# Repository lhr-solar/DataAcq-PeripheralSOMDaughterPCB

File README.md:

# Telemetry Peripheral SOM Daughterboard IMU
Author: Frank Li and Jim Fang

This board takes inputs from an IMU, airflow sensor, and three temp sensors and interfaces with the BPS Leader SOM.

## BOM

[**Mouser Cart**](https://www.mouser.com/ProjectManager/ProjectDetail.aspx?AccessID=6005ad65a9)

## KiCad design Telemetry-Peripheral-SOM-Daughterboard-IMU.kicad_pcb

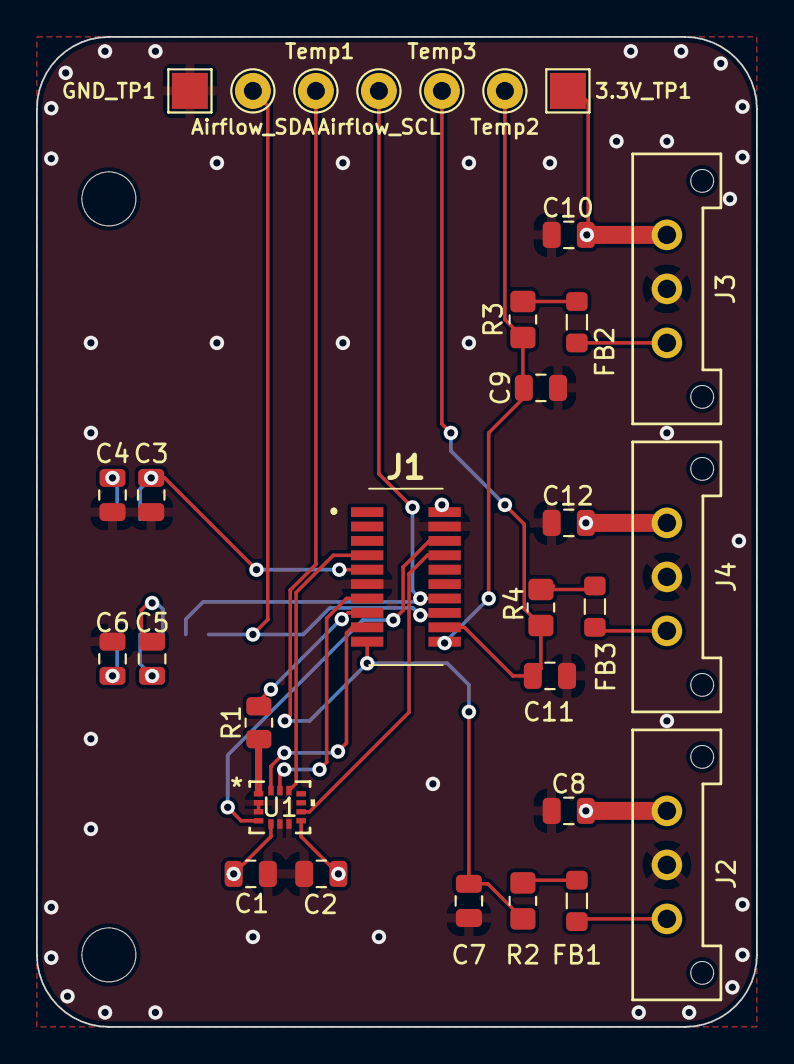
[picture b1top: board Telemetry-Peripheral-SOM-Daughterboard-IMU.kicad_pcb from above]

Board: 2 copper layers, 40.0 x 55.0 mm, 34 parts (1 on the bottom side), 24 nets.

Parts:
3.3V_TP1: TestPoint; TestPoint_Pad_2.0x2.0mm
Airflow_SCL: TestPoint; TestPoint_THTPad_D2.0mm_Drill1.0mm
Airflow_SDA: TestPoint; TestPoint_THTPad_D2.0mm_Drill1.0mm
C1, C2, C3, C4, C5, C8, C10, C12: 0.1u; C_0805_2012Metric
C6: 1u; C_0805_2012Metric
C7, C9, C11: 10n; C_0805_2012Metric
FB1, FB2, FB3: 2.2k; L_0805_2012Metric_Pad1.05x1.20mm_HandSolder
GND_TP1: TestPoint; TestPoint_Pad_2.0x2.0mm
IC1: FS3000-1015; FS30001015
J1: Conn_02x10_Odd_Even; Molex_53307-2071
J2, J3, J4: Conn_01x03_Pin; Molex_MicroFit3.0_1x3xP3.00mm_PolarizingPeg_Vertical
MH1, MH2: M.3; MountingHole_3mm
R1: 50; R_0805_2012Metric
R2, R3, R4: 3k; R_0805_2012Metric_Pad1.20x1.40mm_HandSolder
Temp1, Temp2, Temp3: TestPoint; TestPoint_THTPad_D2.0mm_Drill1.0mm
U1: LSM6DSV; LGA14-L_2P59X3P1X0P5_STM

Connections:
+3.3V: 3.3V_TP1.1, C1.1, C2.1, C3.1, C8.1, C10.1, C12.1, IC1.2 (VIN), J1.2, J1.9, J2.1, J3.1, J4.1, U1.5 (VDD_IO), U1.8 (VDD)
/I2C1_SCL: Airflow_SCL.1, IC1.7 (SCL), J1.14
/I2C1_SDA: Airflow_SDA.1, IC1.6 (SDA), J1.16
/I2C2_SCL: J1.8, U1.9 (INT2)
/I2C2_SDA: J1.6, U1.4 (INT1)
/PA1: C9.1, J1.20, R3.1, Temp2.1
/PA2: C11.1, J1.18, R4.1, Temp3.1
/SPI1_MISO: J1.15, R1.1
/SPI1_MOSI: J1.17, U1.14 (SDA)
/SPI1_NSS: C7.1, J1.19, R2.1, Temp1.1
/SPI1_SCK: J1.13, U1.13 (SCL)
/SPI2_NSS: J1.7, U1.12 (CS)
GND: C1.2, C2.2, C3.2, C4.2, C6.2, C7.2, C8.2, C9.2, C10.2, C11.2, C12.2, GND_TP1.1, IC1.3 (GND), J1.4, J1.11, J2.2, J3.2, J4.2, U1.2 (SDX), U1.3 (SCX), U1.6 (GND), U1.7 (GND)
unnamed: FB1.1, R2.2
unnamed: FB2.1, R3.2
unnamed: FB3.1, R4.2
unnamed: C5.1, IC1.8 (TP1)
unnamed: C5.2, IC1.9 (TP2)
unnamed: C6.1, IC1.10 (VCM)
unnamed: C4.1, IC1.1 (VREG)
unnamed: FB1.2, J2.3
unnamed: FB2.2, J3.3
unnamed: FB3.2, J4.3
unnamed: R1.2, U1.1 (SDO/SA0)

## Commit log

2023-08-28 very basic daughterboard
2023-09-02 Update Telemetry-Peripheral-SOM-Daughterboard-IMU.kicad_sch
    add impedance matching resistor
2023-09-02 Update Telemetry-Peripheral-SOM-Daughterboard-IMU.kicad_pcb
    moved imu to right side of board
2023-09-29 created file for airflow sensor
2023-09-29 created temperature sensor symbol and schematic
2023-09-30 Changes to airflow sch
2023-09-30 updated temperature sensor
2023-09-30 temperatureSensor fix
2023-09-30 fixes to airflow sch
2023-09-30 connected airflow and temperature sensors to connector J1
2023-09-30 fixed errors
2023-09-30 airflow symbols
2023-09-30 temp sensor library fix
2023-09-30 fixed symbol
2023-09-30 fixed symbols
2023-09-30 made imu sensor into a hierarchical sheet
2023-09-30 assigned footprints for all capacitors
2023-10-06 fixed spi1_nss conflict, switched imu to spi2
2023-10-07 first draft
2023-10-07 revision list draft
2023-10-07 added test points in schematic
2023-10-12 a nu start
2023-10-13 fixes
2023-10-14 revision
2023-10-14 PCB layout v1
2023-10-21 Integrated changes made by BPS
2023-10-21 added protective circuitry for temp sensors, made name changes for IMU
2023-10-21 deleted uneeded temp sensor files
2023-10-28 Attempting to merge
2023-10-28 merged
2023-10-28 added datasheet to schematic notes
2023-10-28 datasheet notes
2023-10-28 Name changes
2023-10-28 initial layout
2023-10-28 traces layout
2023-10-28 iteration 2
2023-11-04 PCB changes
2023-11-04 Addressing PCB comments
2023-11-04 Temp sensor layout changes
2023-11-04 extended board for test points and connector
2023-11-04 Added QUAC
2023-11-04 shifted protective circuitry to be closer to connectors
2023-11-04 Aligning components
2023-11-04 Finalizing board layout changes
2023-11-04 added corner stitching and bom folder
2023-11-12 Changes to routing and silkscreen, addressed schematic error
2023-11-13 Removed unconnected trace ends
2023-11-13 Added gerbers
2023-11-14 added a BOM sheet
2023-11-14 changes to BOM sheet
2023-11-18 changes to I2C
2023-11-18 moved testPoints to top of board
2023-11-18 changes to silkscreen naming
2023-11-18 spaced out filtering components
2023-11-21 updated resistor datasheet
2023-11-21 zipped gerbers
2023-11-28 updated constraints and passed DRC
2023-11-28 updated gerbers
2023-12-02 changes to 3K resistor on excel BOM
